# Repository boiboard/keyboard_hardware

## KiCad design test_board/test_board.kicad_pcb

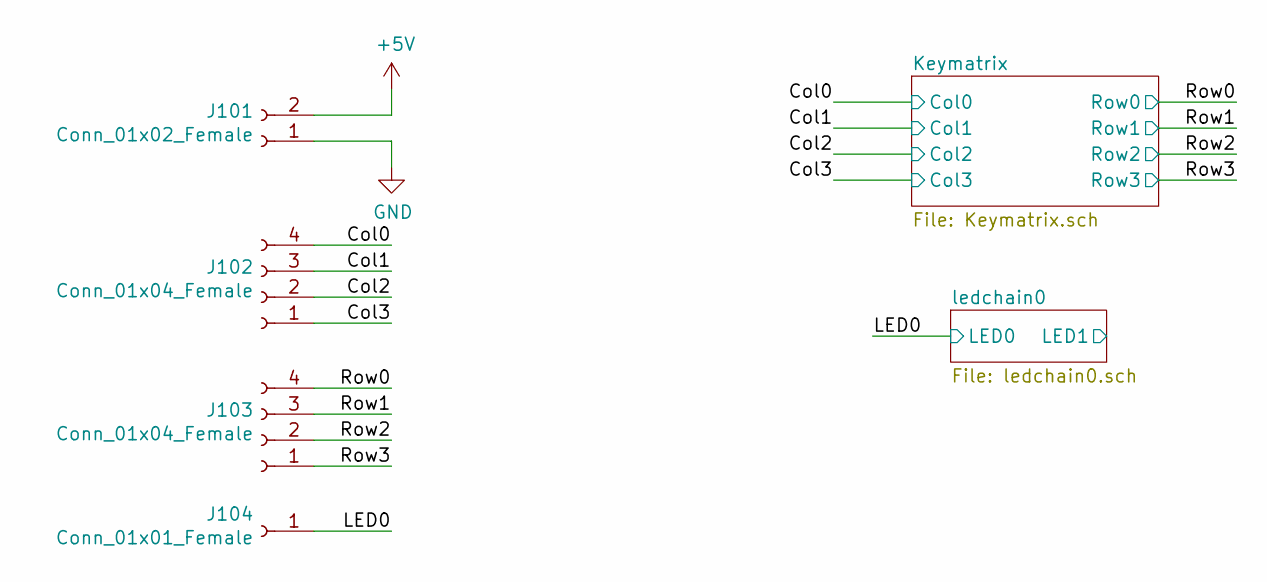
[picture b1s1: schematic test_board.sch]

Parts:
J101: Conn_01x02_Female; PinHeader_1x02_P2.54mm_Vertical
J102, J103: Conn_01x04_Female; PinHeader_1x04_P2.54mm_Vertical
J104: Conn_01x01_Female; PinHeader_1x01_P2.54mm_Vertical

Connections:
+5V: J101.2; also elsewhere on the board
/Col0: J102.4; also elsewhere on the board
/Col1: J102.3; also elsewhere on the board
/Col2: J102.2; also elsewhere on the board
/Col3: J102.1; also elsewhere on the board
/LED0: J104.1; also elsewhere on the board
/Row0: J103.4; also elsewhere on the board
/Row1: J103.3; also elsewhere on the board
/Row2: J103.2; also elsewhere on the board
/Row3: J103.1; also elsewhere on the board
GND: J101.1; also elsewhere on the board

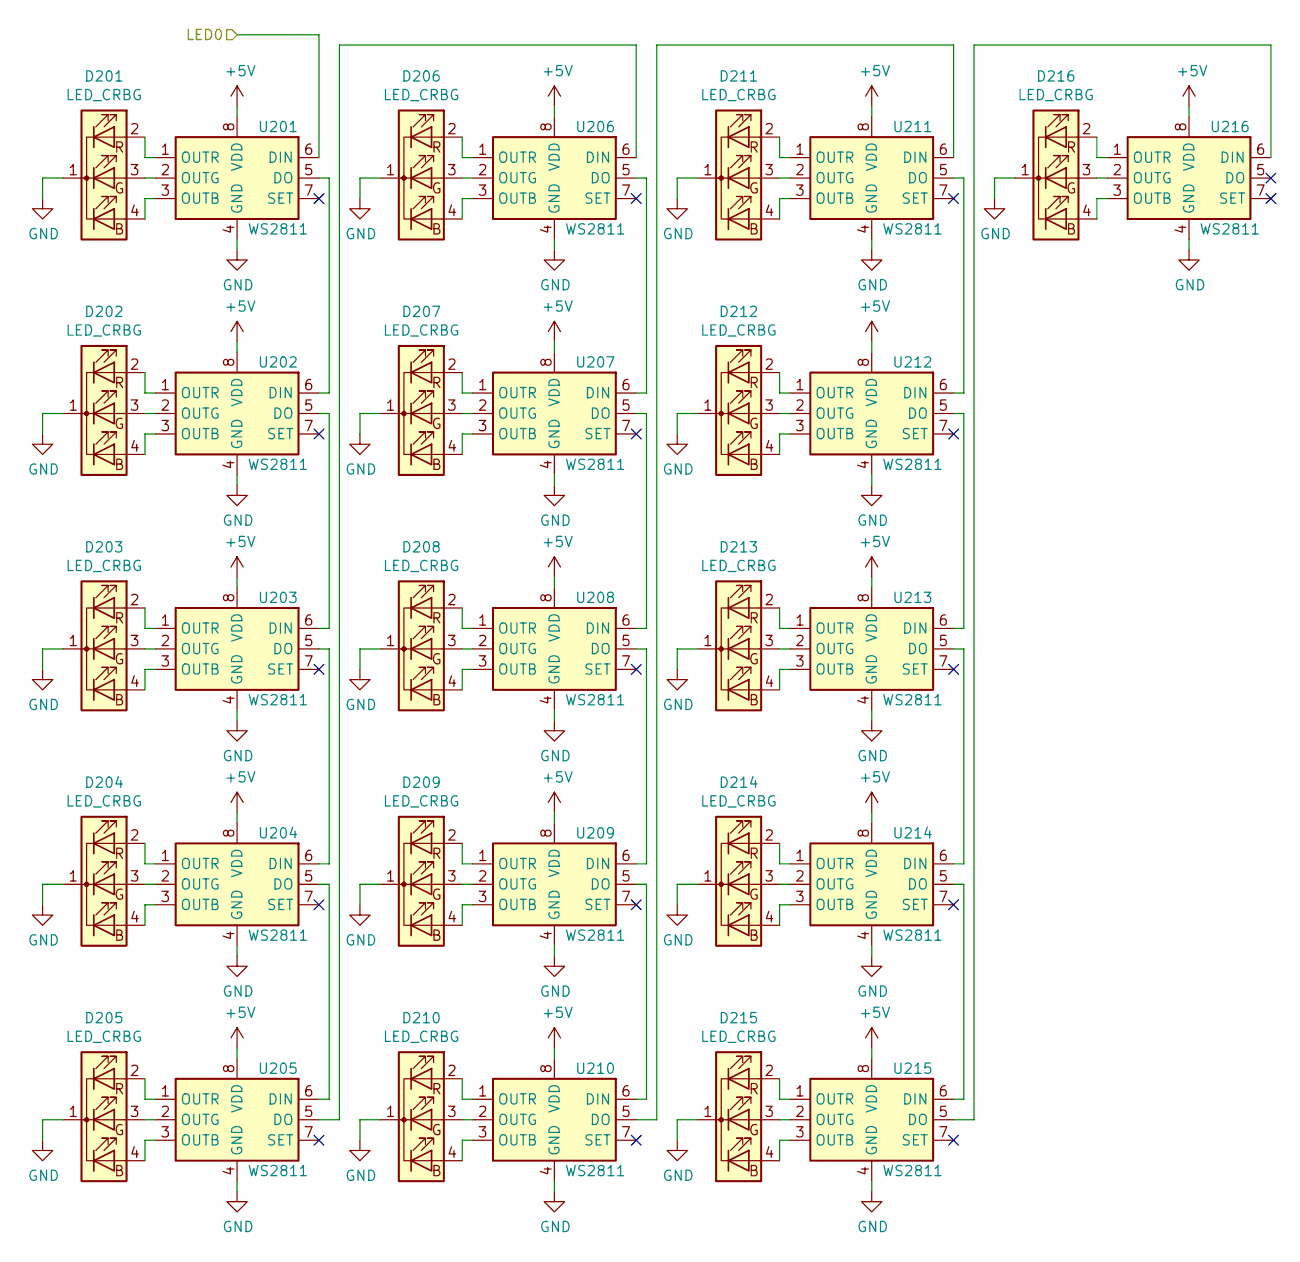
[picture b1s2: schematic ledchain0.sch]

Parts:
D201, D202, D203, D204, D205, D206, D207, D208, D209, D210, D211, D212, D213, D214, D215, D216: LED_CRBG; APTF1616SEJ3ZGGVBDC
U201, U202, U203, U204, U205, U206, U207, U208, U209, U210, U211, U212, U213, U214, U215, U216: WS2811; SOIC-8-1EP_3.9x4.9mm_P1.27mm_EP2.29x3mm

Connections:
+5V: U201.8 (VDD), U202.8 (VDD), U203.8 (VDD), U204.8 (VDD), U205.8 (VDD), U206.8 (VDD), U207.8 (VDD), U208.8 (VDD), U209.8 (VDD), U210.8 (VDD), U211.8 (VDD), U212.8 (VDD), U213.8 (VDD), U214.8 (VDD), U215.8 (VDD), U216.8 (VDD); also elsewhere on the board
/LED0: U201.6 (DIN); also elsewhere on the board
GND: D201.1 (K), D202.1 (K), D203.1 (K), D204.1 (K), D205.1 (K), D206.1 (K), D207.1 (K), D208.1 (K), D209.1 (K), D210.1 (K), D211.1 (K), D212.1 (K), D213.1 (K), D214.1 (K), D215.1 (K), D216.1 (K), U201.4 (GND), U202.4 (GND), U203.4 (GND), U204.4 (GND), U205.4 (GND), U206.4 (GND), U207.4 (GND), U208.4 (GND), U209.4 (GND), U210.4 (GND), U211.4 (GND), U212.4 (GND), U213.4 (GND), U214.4 (GND), U215.4 (GND), U216.4 (GND); also elsewhere on the board
unnamed: D201.2 (RA), U201.1 (OUTR)
unnamed: D201.3 (GA), U201.2 (OUTG)
unnamed: D201.4 (BA), U201.3 (OUTB)
unnamed: D202.2 (RA), U202.1 (OUTR)
unnamed: D202.3 (GA), U202.2 (OUTG)
unnamed: D202.4 (BA), U202.3 (OUTB)
unnamed: D203.2 (RA), U203.1 (OUTR)
unnamed: D203.3 (GA), U203.2 (OUTG)
unnamed: D203.4 (BA), U203.3 (OUTB)
unnamed: D204.2 (RA), U204.1 (OUTR)
unnamed: D204.3 (GA), U204.2 (OUTG)
unnamed: D204.4 (BA), U204.3 (OUTB)
unnamed: D205.2 (RA), U205.1 (OUTR)
unnamed: D205.3 (GA), U205.2 (OUTG)
unnamed: D205.4 (BA), U205.3 (OUTB)
unnamed: D206.2 (RA), U206.1 (OUTR)
unnamed: D206.3 (GA), U206.2 (OUTG)
unnamed: D206.4 (BA), U206.3 (OUTB)
unnamed: D207.2 (RA), U207.1 (OUTR)
unnamed: D207.3 (GA), U207.2 (OUTG)
unnamed: D207.4 (BA), U207.3 (OUTB)
unnamed: D208.2 (RA), U208.1 (OUTR)
unnamed: D208.3 (GA), U208.2 (OUTG)
unnamed: D208.4 (BA), U208.3 (OUTB)
unnamed: D209.2 (RA), U209.1 (OUTR)
unnamed: D209.3 (GA), U209.2 (OUTG)
unnamed: D209.4 (BA), U209.3 (OUTB)
unnamed: D210.2 (RA), U210.1 (OUTR)
unnamed: D210.3 (GA), U210.2 (OUTG)
unnamed: D210.4 (BA), U210.3 (OUTB)
unnamed: D211.2 (RA), U211.1 (OUTR)
unnamed: D211.3 (GA), U211.2 (OUTG)
unnamed: D211.4 (BA), U211.3 (OUTB)
unnamed: D212.2 (RA), U212.1 (OUTR)
unnamed: D212.3 (GA), U212.2 (OUTG)
unnamed: D212.4 (BA), U212.3 (OUTB)
unnamed: D213.2 (RA), U213.1 (OUTR)
unnamed: D213.3 (GA), U213.2 (OUTG)
unnamed: D213.4 (BA), U213.3 (OUTB)
unnamed: D214.2 (RA), U214.1 (OUTR)
unnamed: D214.3 (GA), U214.2 (OUTG)
unnamed: D214.4 (BA), U214.3 (OUTB)
unnamed: D215.2 (RA), U215.1 (OUTR)
unnamed: D215.3 (GA), U215.2 (OUTG)
unnamed: D215.4 (BA), U215.3 (OUTB)
unnamed: D216.2 (RA), U216.1 (OUTR)
unnamed: D216.3 (GA), U216.2 (OUTG)
unnamed: D216.4 (BA), U216.3 (OUTB)
unnamed: U201.5 (DO), U202.6 (DIN)
unnamed: U202.5 (DO), U203.6 (DIN)
unnamed: U203.5 (DO), U204.6 (DIN)
unnamed: U204.5 (DO), U205.6 (DIN)
unnamed: U205.5 (DO), U206.6 (DIN)
unnamed: U206.5 (DO), U207.6 (DIN)
unnamed: U207.5 (DO), U208.6 (DIN)
unnamed: U208.5 (DO), U209.6 (DIN)
unnamed: U209.5 (DO), U210.6 (DIN)
unnamed: U210.5 (DO), U211.6 (DIN)
unnamed: U211.5 (DO), U212.6 (DIN)
unnamed: U212.5 (DO), U213.6 (DIN)
unnamed: U213.5 (DO), U214.6 (DIN)
unnamed: U214.5 (DO), U215.6 (DIN)
unnamed: U215.5 (DO), U216.6 (DIN)

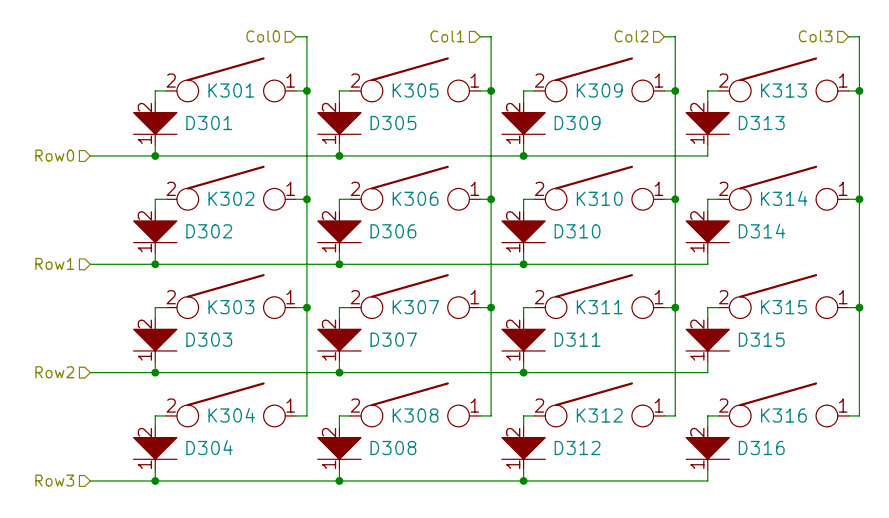
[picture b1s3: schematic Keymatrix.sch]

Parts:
D301, D302, D303, D304, D305, D306, D307, D308, D309, D310, D311, D312, D313, D314, D315, D316: D; D_SOD-523
K301, K302, K303, K304, K305, K306, K307, K308, K309, K310, K311, K312, K313, K314, K315, K316: KEYSW; Kailh_socket

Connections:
/Col0: K301.1, K302.1, K303.1, K304.1; also elsewhere on the board
/Col1: K305.1, K306.1, K307.1, K308.1; also elsewhere on the board
/Col2: K309.1, K310.1, K311.1, K312.1; also elsewhere on the board
/Col3: K313.1, K314.1, K315.1, K316.1; also elsewhere on the board
/Row0: D301.1, D305.1, D309.1, D313.1; also elsewhere on the board
/Row1: D302.1, D306.1, D310.1, D314.1; also elsewhere on the board
/Row2: D303.1, D307.1, D311.1, D315.1; also elsewhere on the board
/Row3: D304.1, D308.1, D312.1, D316.1; also elsewhere on the board
unnamed: D301.2, K301.2
unnamed: D302.2, K302.2
unnamed: D303.2, K303.2
unnamed: D304.2, K304.2
unnamed: D305.2, K305.2
unnamed: D306.2, K306.2
unnamed: D307.2, K307.2
unnamed: D308.2, K308.2
unnamed: D309.2, K309.2
unnamed: D310.2, K310.2
unnamed: D311.2, K311.2
unnamed: D312.2, K312.2
unnamed: D313.2, K313.2
unnamed: D314.2, K314.2
unnamed: D315.2, K315.2
unnamed: D316.2, K316.2

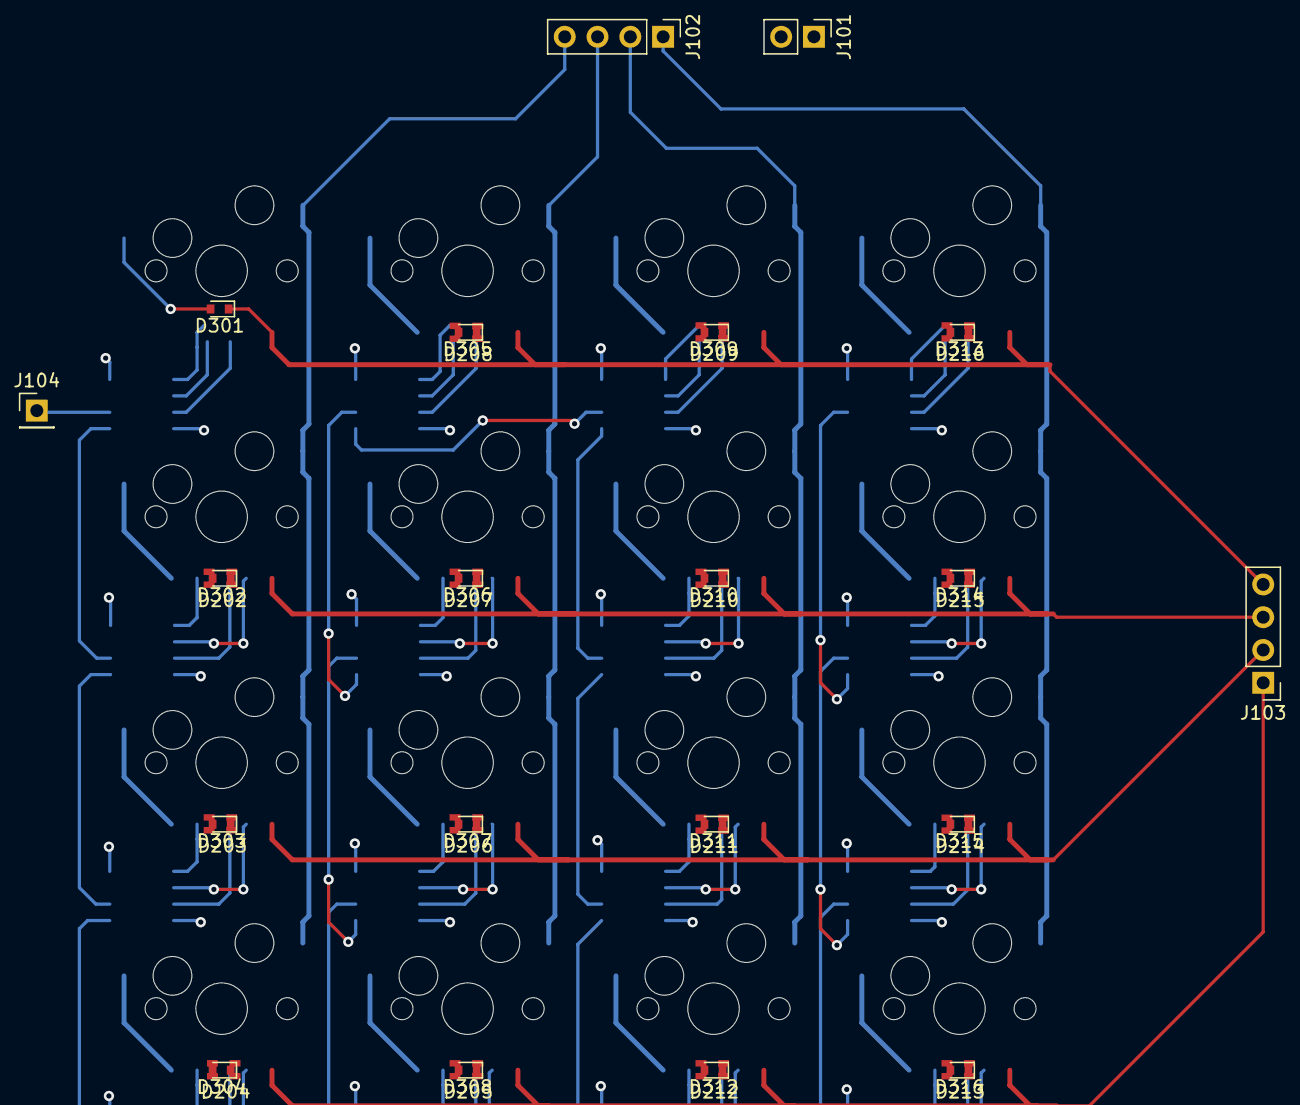
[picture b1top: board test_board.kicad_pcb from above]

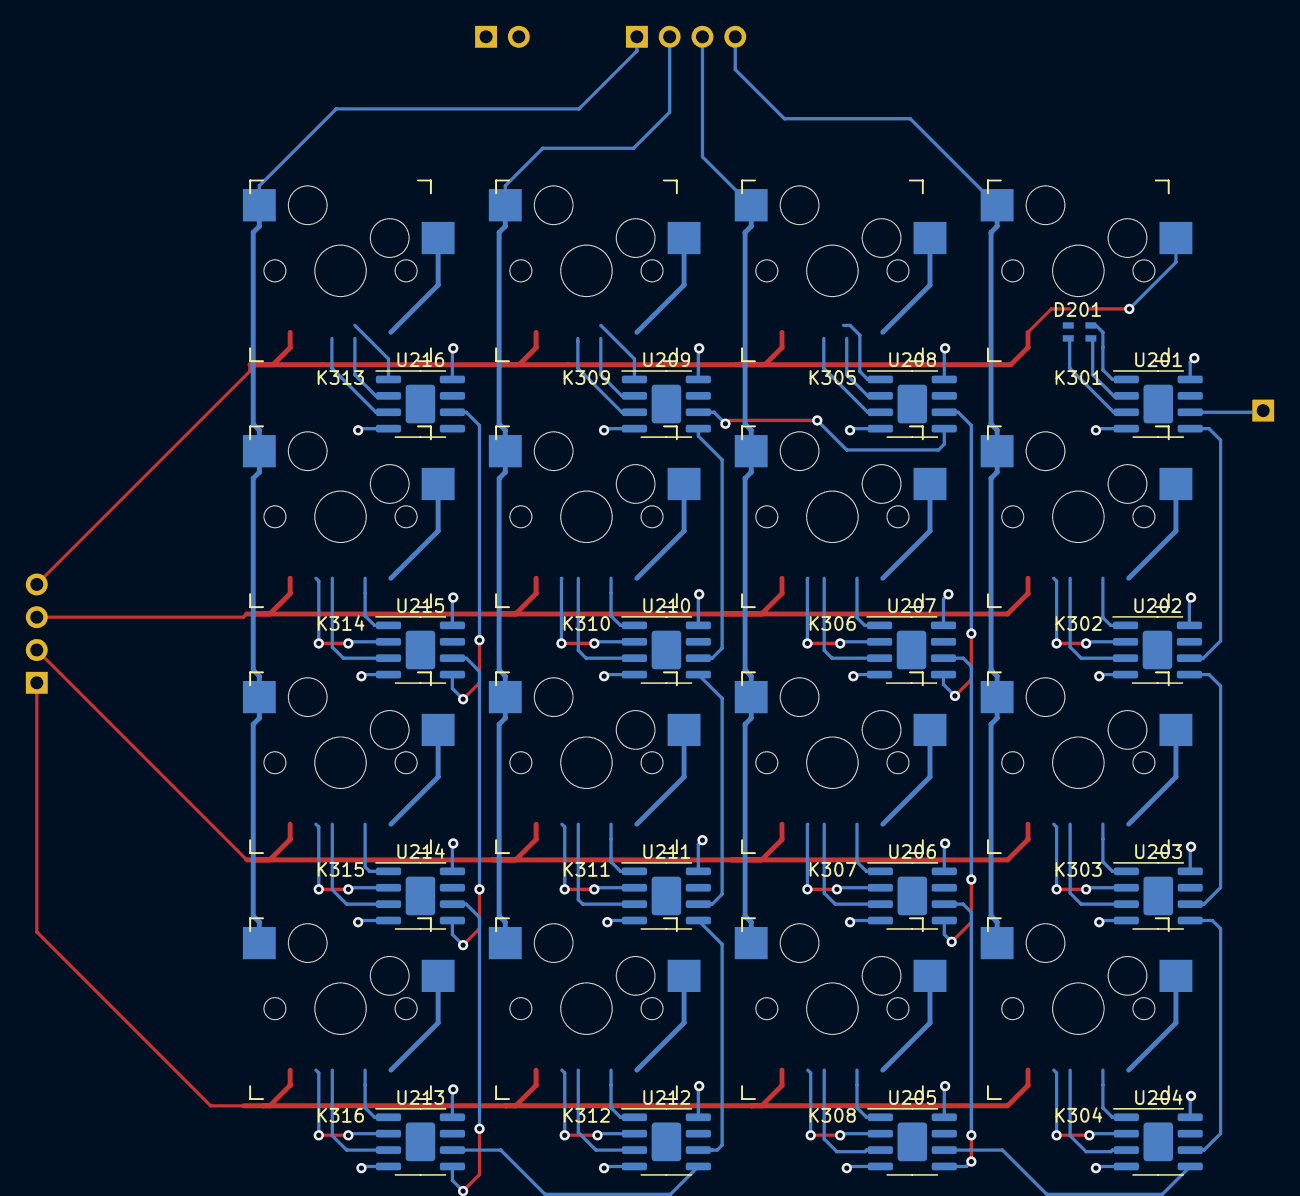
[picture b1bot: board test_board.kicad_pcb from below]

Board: 4 copper layers, 68 parts (17 on the bottom side), 90 nets.

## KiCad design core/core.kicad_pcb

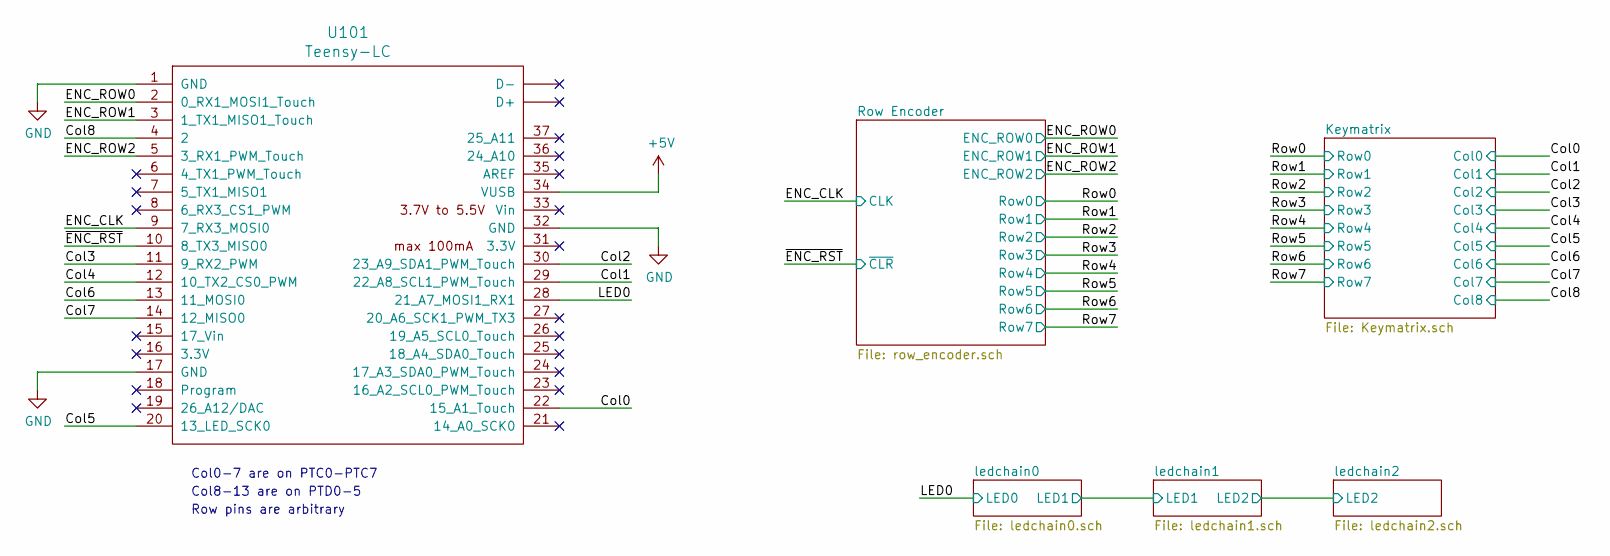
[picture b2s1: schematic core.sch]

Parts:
U101: Teensy-LC; Teensy30_31_32_LC

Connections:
+5V: U101.34 (VUSB); also elsewhere on the board
/Col0: U101.22 (15_A1_Touch); also elsewhere on the board
/Col1: U101.29 (22_A8_SCL1_PWM_Touch); also elsewhere on the board
/Col2: U101.30 (23_A9_SDA1_PWM_Touch); also elsewhere on the board
/Col3: U101.11 (9_RX2_PWM); also elsewhere on the board
/Col4: U101.12 (10_TX2_CS0_PWM); also elsewhere on the board
/Col5: U101.20 (13_LED_SCK0); also elsewhere on the board
/Col6: U101.13 (11_MOSI0); also elsewhere on the board
/Col7: U101.14 (12_MISO0); also elsewhere on the board
/Col8: U101.4 (2); also elsewhere on the board
/ENC_CLK: U101.9 (7_RX3_MOSI0); also elsewhere on the board
/ENC_ROW0: U101.2 (0_RX1_MOSI1_Touch); also elsewhere on the board
/ENC_ROW1: U101.3 (1_TX1_MISO1_Touch); also elsewhere on the board
/ENC_ROW2: U101.5 (3_RX1_PWM_Touch); also elsewhere on the board
/LED0: U101.28 (21_A7_MOSI1_RX1); also elsewhere on the board
/~ENC_RST: U101.10 (8_TX3_MISO0); also elsewhere on the board
GND: U101.1 (GND), U101.17 (GND), U101.32 (GND); also elsewhere on the board

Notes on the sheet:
Col0-7 are on PTC0-PTC7
Col8-13 are on PTD0-5
Row pins are arbitrary

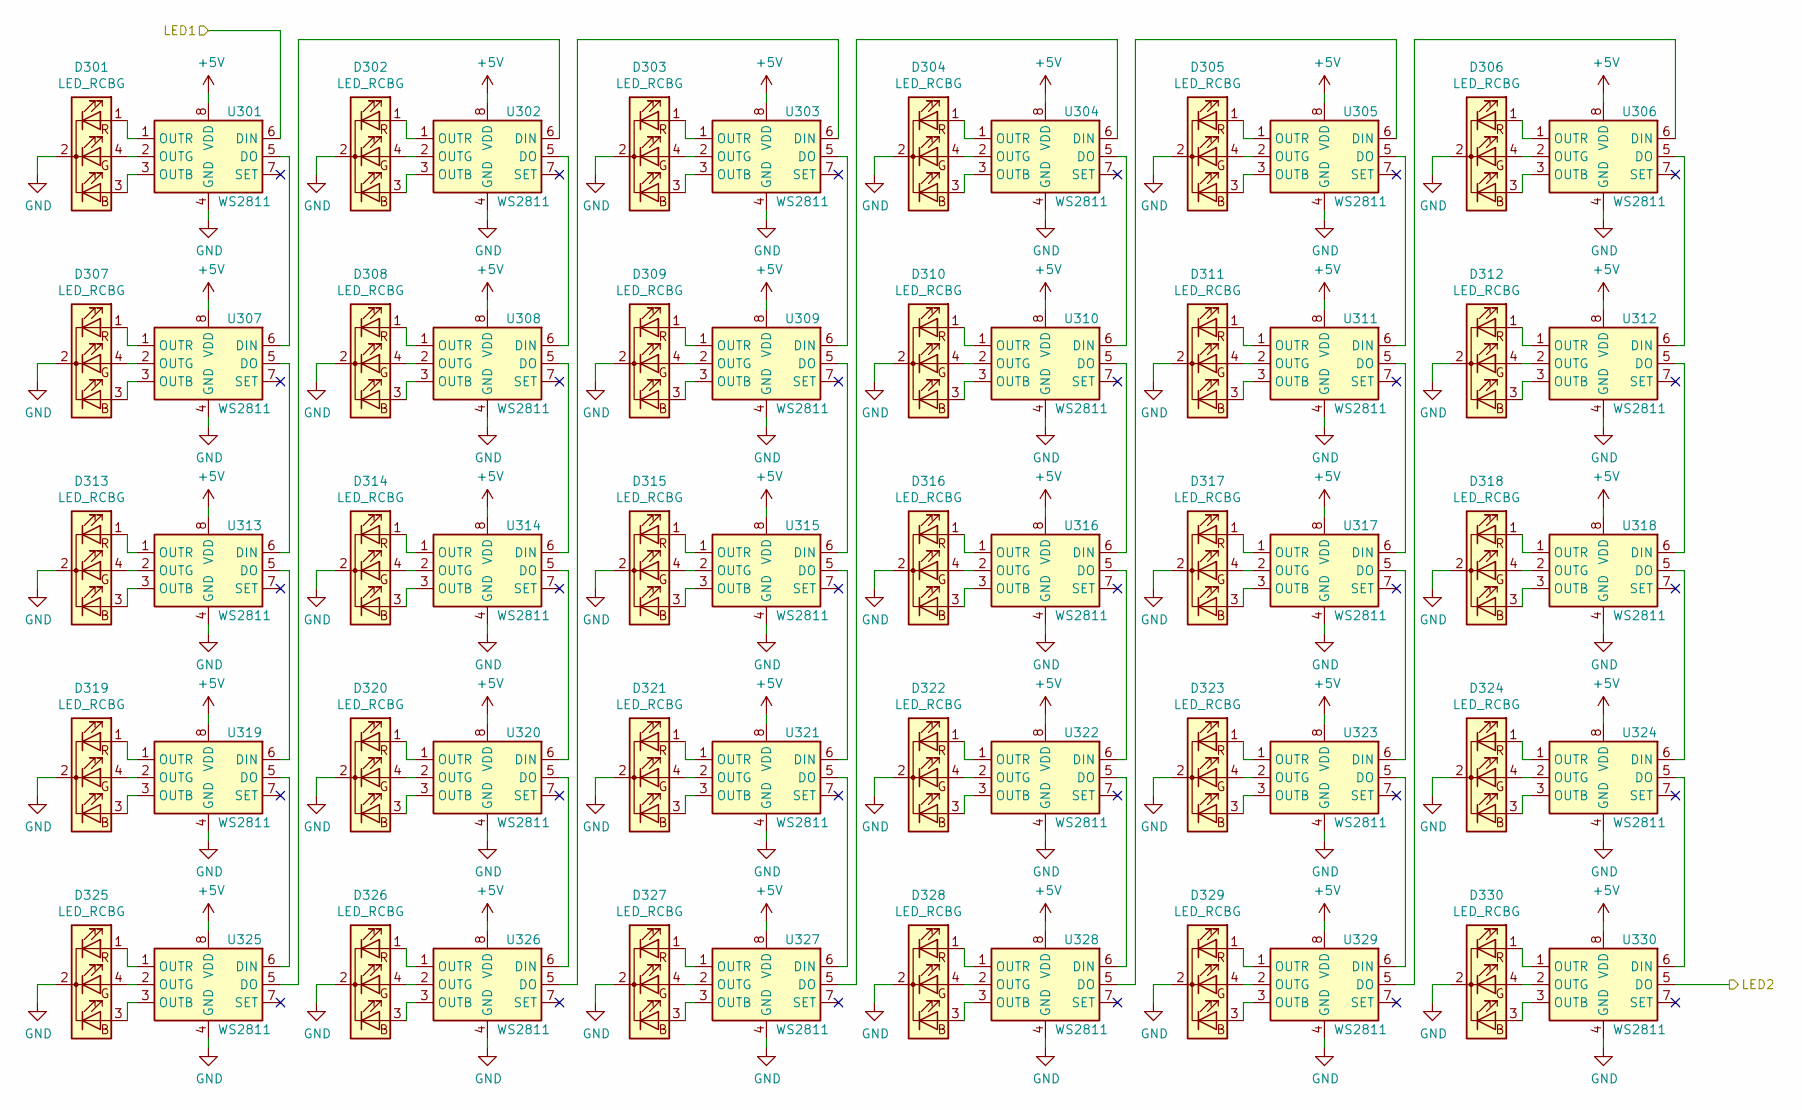
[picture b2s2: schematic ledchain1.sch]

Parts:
D301, D302, D303, D304, D305, D306, D307, D308, D309, D310, D311, D312, D313, D314, D315, D316, D317, D318, D319, D320, D321, D322, D323, D324, D325, D326, D327, D328, D329, D330: LED_RCBG; PinHeader_1x04_P1.00mm_Horizontal
U301, U302, U303, U304, U305, U306, U307, U308, U309, U310, U311, U312, U313, U314, U315, U316, U317, U318, U319, U320, U321, U322, U323, U324, U325, U326, U327, U328, U329, U330: WS2811; SOIC-8-1EP_3.9x4.9mm_P1.27mm_EP2.29x3mm

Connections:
+5V: U301.8 (VDD), U302.8 (VDD), U303.8 (VDD), U304.8 (VDD), U305.8 (VDD), U306.8 (VDD), U307.8 (VDD), U308.8 (VDD), U309.8 (VDD), U310.8 (VDD), U311.8 (VDD), U312.8 (VDD), U313.8 (VDD), U314.8 (VDD), U315.8 (VDD), U316.8 (VDD), U317.8 (VDD), U318.8 (VDD), U319.8 (VDD), U320.8 (VDD), U321.8 (VDD), U322.8 (VDD), U323.8 (VDD), U324.8 (VDD), U325.8 (VDD), U326.8 (VDD), U327.8 (VDD), U328.8 (VDD), U329.8 (VDD), U330.8 (VDD); also elsewhere on the board
/ledchain0/LED1: U301.6 (DIN); also elsewhere on the board
/ledchain1/LED2: U330.5 (DO); also elsewhere on the board
GND: D301.2 (K), D302.2 (K), D303.2 (K), D304.2 (K), D305.2 (K), D306.2 (K), D307.2 (K), D308.2 (K), D309.2 (K), D310.2 (K), D311.2 (K), D312.2 (K), D313.2 (K), D314.2 (K), D315.2 (K), D316.2 (K), D317.2 (K), D318.2 (K), D319.2 (K), D320.2 (K), D321.2 (K), D322.2 (K), D323.2 (K), D324.2 (K), D325.2 (K), D326.2 (K), D327.2 (K), D328.2 (K), D329.2 (K), D330.2 (K), U301.4 (GND), U302.4 (GND), U303.4 (GND), U304.4 (GND), U305.4 (GND), U306.4 (GND), U307.4 (GND), U308.4 (GND), U309.4 (GND), U310.4 (GND), U311.4 (GND), U312.4 (GND), U313.4 (GND), U314.4 (GND), U315.4 (GND), U316.4 (GND), U317.4 (GND), U318.4 (GND), U319.4 (GND), U320.4 (GND), U321.4 (GND), U322.4 (GND), U323.4 (GND), U324.4 (GND), U325.4 (GND), U326.4 (GND), U327.4 (GND), U328.4 (GND), U329.4 (GND), U330.4 (GND); also elsewhere on the board
unnamed: D301.1 (RA), U301.1 (OUTR)
unnamed: D301.3 (BA), U301.3 (OUTB)
unnamed: D301.4 (GA), U301.2 (OUTG)
unnamed: D302.1 (RA), U302.1 (OUTR)
unnamed: D302.3 (BA), U302.3 (OUTB)
unnamed: D302.4 (GA), U302.2 (OUTG)
unnamed: D303.1 (RA), U303.1 (OUTR)
unnamed: D303.3 (BA), U303.3 (OUTB)
unnamed: D303.4 (GA), U303.2 (OUTG)
unnamed: D304.1 (RA), U304.1 (OUTR)
unnamed: D304.3 (BA), U304.3 (OUTB)
unnamed: D304.4 (GA), U304.2 (OUTG)
unnamed: D305.1 (RA), U305.1 (OUTR)
unnamed: D305.3 (BA), U305.3 (OUTB)
unnamed: D305.4 (GA), U305.2 (OUTG)
unnamed: D306.1 (RA), U306.1 (OUTR)
unnamed: D306.3 (BA), U306.3 (OUTB)
unnamed: D306.4 (GA), U306.2 (OUTG)
unnamed: D307.1 (RA), U307.1 (OUTR)
unnamed: D307.3 (BA), U307.3 (OUTB)
unnamed: D307.4 (GA), U307.2 (OUTG)
unnamed: D308.1 (RA), U308.1 (OUTR)
unnamed: D308.3 (BA), U308.3 (OUTB)
unnamed: D308.4 (GA), U308.2 (OUTG)
unnamed: D309.1 (RA), U309.1 (OUTR)
unnamed: D309.3 (BA), U309.3 (OUTB)
unnamed: D309.4 (GA), U309.2 (OUTG)
unnamed: D310.1 (RA), U310.1 (OUTR)
unnamed: D310.3 (BA), U310.3 (OUTB)
unnamed: D310.4 (GA), U310.2 (OUTG)
unnamed: D311.1 (RA), U311.1 (OUTR)
unnamed: D311.3 (BA), U311.3 (OUTB)
unnamed: D311.4 (GA), U311.2 (OUTG)
unnamed: D312.1 (RA), U312.1 (OUTR)
unnamed: D312.3 (BA), U312.3 (OUTB)
unnamed: D312.4 (GA), U312.2 (OUTG)
unnamed: D313.1 (RA), U313.1 (OUTR)
unnamed: D313.3 (BA), U313.3 (OUTB)
unnamed: D313.4 (GA), U313.2 (OUTG)
unnamed: D314.1 (RA), U314.1 (OUTR)
unnamed: D314.3 (BA), U314.3 (OUTB)
unnamed: D314.4 (GA), U314.2 (OUTG)
unnamed: D315.1 (RA), U315.1 (OUTR)
unnamed: D315.3 (BA), U315.3 (OUTB)
unnamed: D315.4 (GA), U315.2 (OUTG)
unnamed: D316.1 (RA), U316.1 (OUTR)
unnamed: D316.3 (BA), U316.3 (OUTB)
unnamed: D316.4 (GA), U316.2 (OUTG)
unnamed: D317.1 (RA), U317.1 (OUTR)
unnamed: D317.3 (BA), U317.3 (OUTB)
unnamed: D317.4 (GA), U317.2 (OUTG)
unnamed: D318.1 (RA), U318.1 (OUTR)
unnamed: D318.3 (BA), U318.3 (OUTB)
unnamed: D318.4 (GA), U318.2 (OUTG)
unnamed: D319.1 (RA), U319.1 (OUTR)
unnamed: D319.3 (BA), U319.3 (OUTB)
unnamed: D319.4 (GA), U319.2 (OUTG)
unnamed: D320.1 (RA), U320.1 (OUTR)
unnamed: D320.3 (BA), U320.3 (OUTB)
unnamed: D320.4 (GA), U320.2 (OUTG)
unnamed: D321.1 (RA), U321.1 (OUTR)
unnamed: D321.3 (BA), U321.3 (OUTB)
unnamed: D321.4 (GA), U321.2 (OUTG)
unnamed: D322.1 (RA), U322.1 (OUTR)
unnamed: D322.3 (BA), U322.3 (OUTB)
unnamed: D322.4 (GA), U322.2 (OUTG)
unnamed: D323.1 (RA), U323.1 (OUTR)
unnamed: D323.3 (BA), U323.3 (OUTB)
unnamed: D323.4 (GA), U323.2 (OUTG)
unnamed: D324.1 (RA), U324.1 (OUTR)
unnamed: D324.3 (BA), U324.3 (OUTB)
unnamed: D324.4 (GA), U324.2 (OUTG)
unnamed: D325.1 (RA), U325.1 (OUTR)
unnamed: D325.3 (BA), U325.3 (OUTB)
unnamed: D325.4 (GA), U325.2 (OUTG)
unnamed: D326.1 (RA), U326.1 (OUTR)
unnamed: D326.3 (BA), U326.3 (OUTB)
unnamed: D326.4 (GA), U326.2 (OUTG)
unnamed: D327.1 (RA), U327.1 (OUTR)
unnamed: D327.3 (BA), U327.3 (OUTB)
unnamed: D327.4 (GA), U327.2 (OUTG)
unnamed: D328.1 (RA), U328.1 (OUTR)
unnamed: D328.3 (BA), U328.3 (OUTB)
unnamed: D328.4 (GA), U328.2 (OUTG)
unnamed: D329.1 (RA), U329.1 (OUTR)
unnamed: D329.3 (BA), U329.3 (OUTB)
unnamed: D329.4 (GA), U329.2 (OUTG)
unnamed: D330.1 (RA), U330.1 (OUTR)
unnamed: D330.3 (BA), U330.3 (OUTB)
unnamed: D330.4 (GA), U330.2 (OUTG)
unnamed: U301.5 (DO), U307.6 (DIN)
unnamed: U302.5 (DO), U308.6 (DIN)
unnamed: U302.6 (DIN), U325.5 (DO)
unnamed: U303.5 (DO), U309.6 (DIN)
unnamed: U303.6 (DIN), U326.5 (DO)
unnamed: U304.5 (DO), U310.6 (DIN)
unnamed: U304.6 (DIN), U327.5 (DO)
unnamed: U305.5 (DO), U311.6 (DIN)
unnamed: U305.6 (DIN), U328.5 (DO)
unnamed: U306.5 (DO), U312.6 (DIN)
unnamed: U306.6 (DIN), U329.5 (DO)
unnamed: U307.5 (DO), U313.6 (DIN)
unnamed: U308.5 (DO), U314.6 (DIN)
unnamed: U309.5 (DO), U315.6 (DIN)
unnamed: U310.5 (DO), U316.6 (DIN)
unnamed: U311.5 (DO), U317.6 (DIN)
unnamed: U312.5 (DO), U318.6 (DIN)
unnamed: U313.5 (DO), U319.6 (DIN)
unnamed: U314.5 (DO), U320.6 (DIN)
unnamed: U315.5 (DO), U321.6 (DIN)
unnamed: U316.5 (DO), U322.6 (DIN)
unnamed: U317.5 (DO), U323.6 (DIN)
unnamed: U318.5 (DO), U324.6 (DIN)
unnamed: U319.5 (DO), U325.6 (DIN)
unnamed: U320.5 (DO), U326.6 (DIN)
unnamed: U321.5 (DO), U327.6 (DIN)
unnamed: U322.5 (DO), U328.6 (DIN)
unnamed: U323.5 (DO), U329.6 (DIN)
unnamed: U324.5 (DO), U330.6 (DIN)

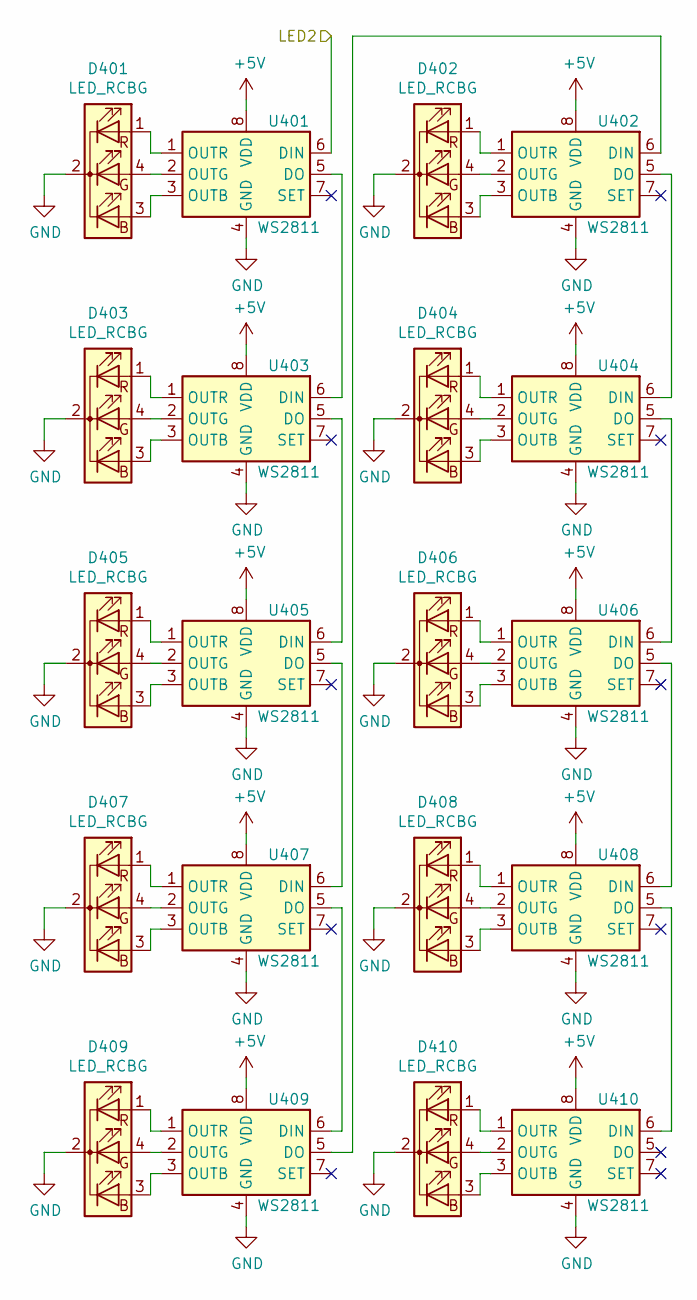
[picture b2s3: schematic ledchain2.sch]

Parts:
D401, D402, D403, D404, D405, D406, D407, D408, D409, D410: LED_RCBG; PinHeader_1x04_P1.00mm_Horizontal
U401, U402, U403, U404, U405, U406, U407, U408, U409, U410: WS2811; SOIC-8-1EP_3.9x4.9mm_P1.27mm_EP2.29x3mm

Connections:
+5V: U401.8 (VDD), U402.8 (VDD), U403.8 (VDD), U404.8 (VDD), U405.8 (VDD), U406.8 (VDD), U407.8 (VDD), U408.8 (VDD), U409.8 (VDD), U410.8 (VDD); also elsewhere on the board
/ledchain1/LED2: U401.6 (DIN); also elsewhere on the board
GND: D401.2 (K), D402.2 (K), D403.2 (K), D404.2 (K), D405.2 (K), D406.2 (K), D407.2 (K), D408.2 (K), D409.2 (K), D410.2 (K), U401.4 (GND), U402.4 (GND), U403.4 (GND), U404.4 (GND), U405.4 (GND), U406.4 (GND), U407.4 (GND), U408.4 (GND), U409.4 (GND), U410.4 (GND); also elsewhere on the board
unnamed: D401.1 (RA), U401.1 (OUTR)
unnamed: D401.3 (BA), U401.3 (OUTB)
unnamed: D401.4 (GA), U401.2 (OUTG)
unnamed: D402.1 (RA), U402.1 (OUTR)
unnamed: D402.3 (BA), U402.3 (OUTB)
unnamed: D402.4 (GA), U402.2 (OUTG)
unnamed: D403.1 (RA), U403.1 (OUTR)
unnamed: D403.3 (BA), U403.3 (OUTB)
unnamed: D403.4 (GA), U403.2 (OUTG)
unnamed: D404.1 (RA), U404.1 (OUTR)
unnamed: D404.3 (BA), U404.3 (OUTB)
unnamed: D404.4 (GA), U404.2 (OUTG)
unnamed: D405.1 (RA), U405.1 (OUTR)
unnamed: D405.3 (BA), U405.3 (OUTB)
unnamed: D405.4 (GA), U405.2 (OUTG)
unnamed: D406.1 (RA), U406.1 (OUTR)
unnamed: D406.3 (BA), U406.3 (OUTB)
unnamed: D406.4 (GA), U406.2 (OUTG)
unnamed: D407.1 (RA), U407.1 (OUTR)
unnamed: D407.3 (BA), U407.3 (OUTB)
unnamed: D407.4 (GA), U407.2 (OUTG)
unnamed: D408.1 (RA), U408.1 (OUTR)
unnamed: D408.3 (BA), U408.3 (OUTB)
unnamed: D408.4 (GA), U408.2 (OUTG)
unnamed: D409.1 (RA), U409.1 (OUTR)
unnamed: D409.3 (BA), U409.3 (OUTB)
unnamed: D409.4 (GA), U409.2 (OUTG)
unnamed: D410.1 (RA), U410.1 (OUTR)
unnamed: D410.3 (BA), U410.3 (OUTB)
unnamed: D410.4 (GA), U410.2 (OUTG)
unnamed: U401.5 (DO), U403.6 (DIN)
unnamed: U402.5 (DO), U404.6 (DIN)
unnamed: U402.6 (DIN), U409.5 (DO)
unnamed: U403.5 (DO), U405.6 (DIN)
unnamed: U404.5 (DO), U406.6 (DIN)
unnamed: U405.5 (DO), U407.6 (DIN)
unnamed: U406.5 (DO), U408.6 (DIN)
unnamed: U407.5 (DO), U409.6 (DIN)
unnamed: U408.5 (DO), U410.6 (DIN)

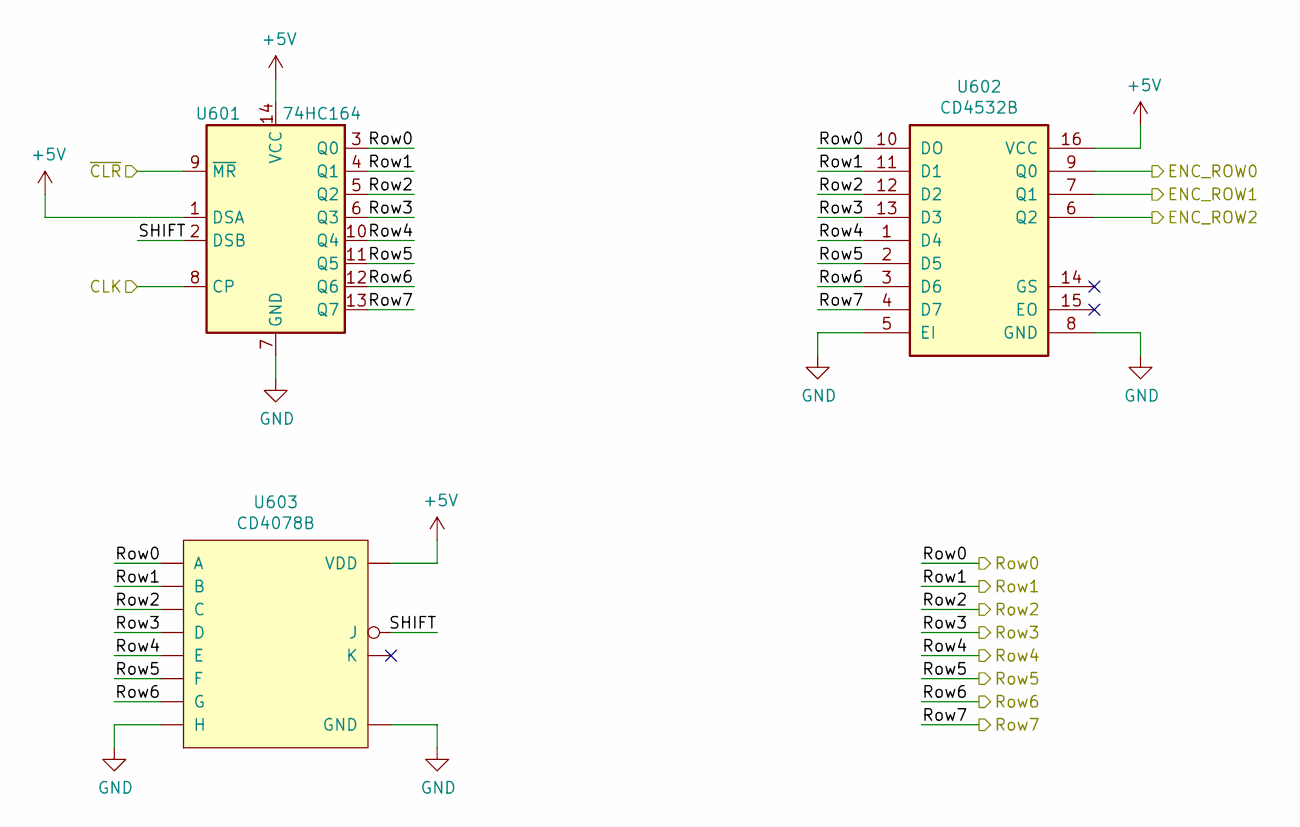
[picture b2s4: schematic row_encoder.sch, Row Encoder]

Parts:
U601: 74HC164; SOIC-14_3.9x8.7mm_P1.27mm
U602: CD4532B; SOIC-16_3.9x9.9mm_P1.27mm
U603: CD4078B; SOIC-14_3.9x8.7mm_P1.27mm

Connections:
+5V: U601.1 (DSA), U601.14 (VCC), U602.16 (VCC), U603.14 (VDD); also elsewhere on the board
/ENC_CLK: U601.8 (CP); also elsewhere on the board
/ENC_ROW0: U602.9 (Q0); also elsewhere on the board
/ENC_ROW1: U602.7 (Q1); also elsewhere on the board
/ENC_ROW2: U602.6 (Q2); also elsewhere on the board
/Row0: U601.3 (Q0), U602.10 (DO), U603.2 (A); also elsewhere on the board
/Row1: U601.4 (Q1), U602.11 (D1), U603.3 (B); also elsewhere on the board
/Row2: U601.5 (Q2), U602.12 (D2), U603.4 (C); also elsewhere on the board
/Row3: U601.6 (Q3), U602.13 (D3), U603.5 (D); also elsewhere on the board
/Row4: U601.10 (Q4), U602.1 (D4), U603.9 (E); also elsewhere on the board
/Row5: U601.11 (Q5), U602.2 (D5), U603.10 (F); also elsewhere on the board
/Row6: U601.12 (Q6), U602.3 (D6), U603.11 (G); also elsewhere on the board
/Row7: U601.13 (Q7), U602.4 (D7); also elsewhere on the board
/Row Encoder/SHIFT: U601.2 (DSB), U603.13 (J)
/~ENC_RST: U601.9 (~MR); also elsewhere on the board
GND: U601.7 (GND), U602.5 (EI), U602.8 (GND), U603.7 (GND), U603.12 (H); also elsewhere on the board
